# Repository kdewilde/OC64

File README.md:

# OC64
MX Compatible ortholinear PCB for the commodore case

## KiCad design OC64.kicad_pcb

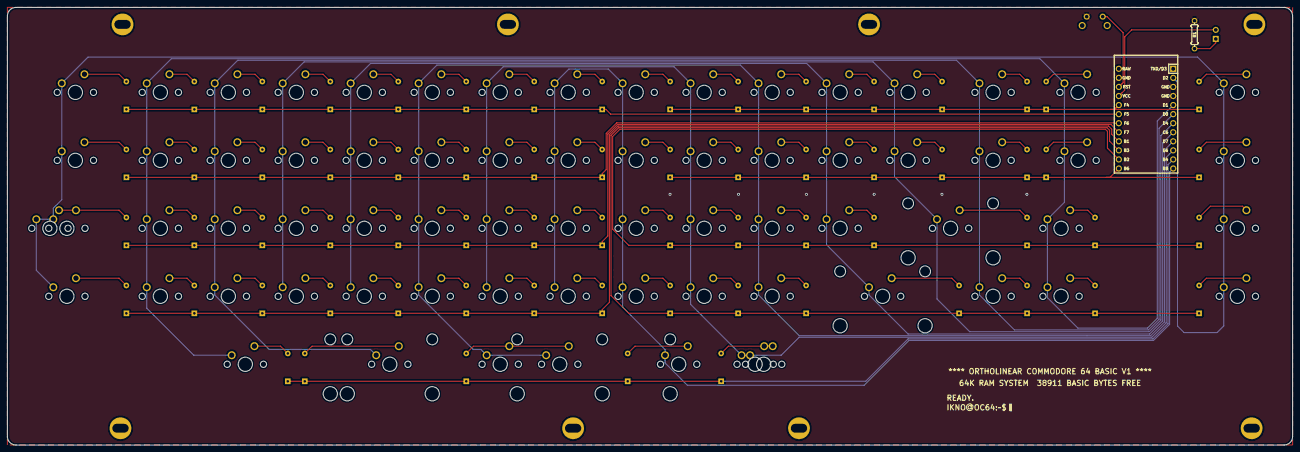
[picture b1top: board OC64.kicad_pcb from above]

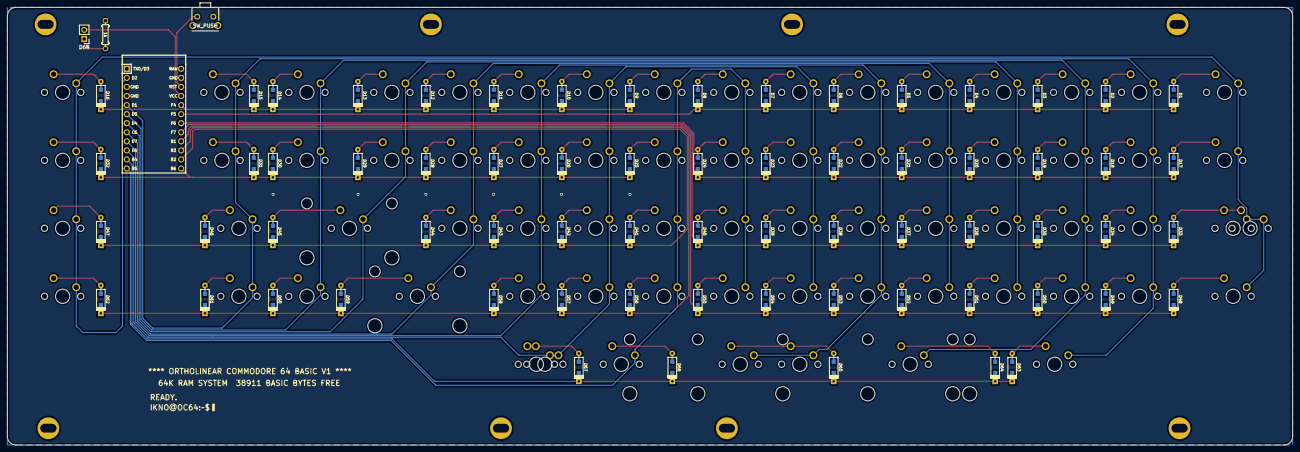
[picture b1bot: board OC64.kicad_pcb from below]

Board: 2 copper layers, 360.2 x 122.6 mm, 149 parts (71 on the bottom side), 88 nets.

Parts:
D1, D2, D3, D4, D5, D6, D7, D8, D9, D10, D11, D12, D13, D14, D15, D16, D17, D18, D19, D20, D21, D22, D23, D24, D25, D26, D27, D28, D29, D30, D31, D32, D33, D34, D35, D36, D37, D38, D39, D40, D41, D42, D43, D44, D45, D46, D47, D48, D49, D50, D51, D52, D53, D54, D55, D56, D57, D58, D59, D60, D61, D62, D63, D64, D65, D66, D67: D; D_SOD123_axial
D68: LED; PinHeader_1x02_P2.54mm_Vertical
H1, H2, H3, H4, H5, H6, H7, H8: MountingHole; Poker_oval_hole
R1: 1k; Resistor-Compact
RSW1: SW_PUSH; SW_TACT_TH_HORIZ
SW1: SW_ESC; MXOnly-1.5U
SW2: SW_1; MXOnly-1U
SW3: SW_2; MXOnly-1U
SW4: SW_3; MXOnly-1U
SW5: SW_4; MXOnly-1U
SW6: SW_5; MXOnly-1U
SW7: SW_6; MXOnly-1U
SW8: SW_7; MXOnly-1U
SW9: SW_8; MXOnly-1U
SW10: SW_9; MXOnly-1U
SW11: SW_0; MXOnly-1U
SW12: SW_-; MXOnly-1U
SW13: SW_=; MXOnly-1U
SW14: SW_BACK; MXOnly-1.5U
SW15: SW_DEL; MXOnly-1U
SW16: SW_F1; MXOnly-1.5U
SW17: SW_TAB; MXOnly-1.5U
SW18: SW_Q; MXOnly-1U
SW19: SW_W; MXOnly-1U
SW20: SW_E; MXOnly-1U
SW21: SW_R; MXOnly-1U
SW22: SW_T; MXOnly-1U
SW23: SW_Y; MXOnly-1U
SW24: SW_U; MXOnly-1U
SW25: SW_I; MXOnly-1U
SW26: SW_O; MXOnly-1U
SW27: SW_P; MXOnly-1U
SW28: SW_[; MXOnly-1U
SW29: SW_]; MXOnly-1U
SW30: SW_\; MXOnly-1.5U
SW31: SW_PGUP; MXOnly-1U
SW32: SW_F2; MXOnly-1.5U
SW33-1: SW_STPCAP; MXOnly-1.75USTEPPED
SW33-2: SW_CAPS; MXOnly-1.75U
SW34: SW_A; MXOnly-1U
SW35: SW_S; MXOnly-1U
SW36: SW_D; MXOnly-1U
SW37: SW_F; MXOnly-1U
SW38: SW_G; MXOnly-1U
SW39: SW_H; MXOnly-1U
SW40: SW_J; MXOnly-1U
SW41: SW_K; MXOnly-1U
SW42: SW_L; MXOnly-1U
SW43: SW_;; MXOnly-1U
SW44: SW_'; MXOnly-1U
SW45: SW_RET; MXOnly-2.25U
SW46: SW_PGDN; MXOnly-1U
SW47: SW_F3; MXOnly-1.5U
SW48: SW_SHIFT; MXOnly-1.75U
SW49: SW_Z; MXOnly-1U
SW50: SW_X; MXOnly-1U
SW51: SW_C; MXOnly-1U
SW52: SW_V; MXOnly-1U
SW53: SW_B; MXOnly-1U
SW54: SW_N; MXOnly-1U
SW55: SW_M; MXOnly-1U
SW56: SW_,; MXOnly-1U
SW57: SW_.; MXOnly-1U
SW58: SW_/; MXOnly-1U
SW59: SW_SHIFT; MXOnly-2.25U
SW60: SW_HOME; MXOnly-1U
SW61: SW_END; MXOnly-1U
SW62: SW_F4; MXOnly-1.5U
SW63: SW_CTRL; MXOnly-1.5U
SW64: SW_LSPAC; MXOnly-2.75U
SW65-1: SW_SPACE; MXOnly-6U
SW65-2: SW_RSPAC; MXOnly-2.25U
SW66: SW_ALT; MXOnly-1.25U
SW67-1: SW_META; MXOnly-1.25U
SW67-2: SW_META; MXOnly-1.5U
U1: ProMicro; ArduinoProMicro

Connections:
GND: R1.1, RSW1.2, U1.3, U1.4, U1.23
unnamed: D1.2, SW1.2
unnamed: D2.2, SW2.2
unnamed: D3.2, SW3.2
unnamed: D4.2, SW4.2
unnamed: D5.2, SW5.2
unnamed: D6.2, SW6.2
unnamed: D7.2, SW7.2
unnamed: D8.2, SW8.2
unnamed: D9.2, SW9.2
unnamed: D10.2, SW10.2
unnamed: D11.2, SW11.2
unnamed: D12.2, SW12.2
unnamed: D13.2, SW13.2
unnamed: D14.2, SW14.2
unnamed: D15.2, SW15.2
unnamed: D16.2, SW16.2
unnamed: D17.2, SW17.2
unnamed: D18.2, SW18.2
unnamed: D19.2, SW19.2
unnamed: D20.2, SW20.2
unnamed: D21.2, SW21.2
unnamed: D22.2, SW22.2
unnamed: D23.2, SW23.2
unnamed: D24.2, SW24.2
unnamed: D25.2, SW25.2
unnamed: D26.2, SW26.2
unnamed: D27.2, SW27.2
unnamed: D28.2, SW28.2
unnamed: D29.2, SW29.2
unnamed: D30.2, SW30.2
unnamed: D31.2, SW31.2
unnamed: D32.2, SW32.2
unnamed: D33.2, SW33-1.2, SW33-2.2
unnamed: D34.2, SW34.2
unnamed: D35.2, SW35.2
unnamed: D36.2, SW36.2
unnamed: D37.2, SW37.2
unnamed: D38.2, SW38.2
unnamed: D39.2, SW39.2
unnamed: D40.2, SW40.2
unnamed: D41.2, SW41.2
unnamed: D42.2, SW42.2
unnamed: D43.2, SW43.2
unnamed: D44.2, SW44.2
unnamed: D45.2, SW45.2
unnamed: D46.2, SW46.2
unnamed: D47.2, SW47.2
unnamed: D48.2, SW48.2
unnamed: D49.2, SW49.2
unnamed: D50.2, SW50.2
unnamed: D51.2, SW51.2
unnamed: D52.2, SW52.2
unnamed: D53.2, SW53.2
unnamed: D54.2, SW54.2
unnamed: D55.2, SW55.2
unnamed: D56.2, SW56.2
unnamed: D57.2, SW57.2
unnamed: D58.2, SW58.2
unnamed: D59.2, SW59.2
unnamed: D60.2, SW60.2
unnamed: D61.2, SW61.2
unnamed: D62.2, SW62.2
unnamed: D63.2, SW63.2
unnamed: D64.2, SW64.2
unnamed: D65.2, SW65-1.2, SW65-2.2
unnamed: D66.2, SW66.2
unnamed: D67.2, SW67-1.2, SW67-2.2
unnamed: D68.1, R1.2
VCC: D68.2, U1.21
col0: SW1.1, SW16.1, SW17.1, SW32.1, SW33-1.1, SW33-2.1, SW47.1, SW48.1, SW62.1, U1.2
col1: SW2.1, SW15.1, SW18.1, SW31.1, SW34.1, SW46.1, SW49.1, SW61.1, SW63.1, U1.5
col2: SW3.1, SW14.1, SW19.1, SW30.1, SW35.1, SW50.1, SW60.1, SW64.1, U1.6
col3: SW4.1, SW13.1, SW20.1, SW29.1, SW36.1, SW45.1, SW51.1, U1.7
col4: SW5.1, SW12.1, SW21.1, SW28.1, SW37.1, SW44.1, SW52.1, SW59.1, U1.8
col5: SW6.1, SW11.1, SW22.1, SW27.1, SW38.1, SW43.1, SW53.1, SW58.1, SW65-1.1, SW65-2.1, U1.9
col6: SW7.1, SW10.1, SW23.1, SW26.1, SW39.1, SW42.1, SW54.1, SW57.1, SW67-1.1, SW67-2.1, U1.10
col7: SW8.1, SW9.1, SW24.1, SW25.1, SW40.1, SW41.1, SW55.1, SW56.1, SW66.1, U1.12
reset: RSW1.1, U1.22
row0: D1.1, D2.1, D3.1, D4.1, D5.1, D6.1, D7.1, D8.1, U1.19
row1: D9.1, D10.1, D11.1, D12.1, D13.1, D14.1, D15.1, D16.1, U1.20
row2: D17.1, D18.1, D19.1, D20.1, D21.1, D22.1, D23.1, D24.1, U1.18
row3: D25.1, D26.1, D27.1, D28.1, D29.1, D30.1, D31.1, D32.1, U1.13
row4: D33.1, D34.1, D35.1, D36.1, D37.1, D38.1, D39.1, D40.1, U1.17
row5: D41.1, D42.1, D43.1, D44.1, D45.1, D46.1, D47.1, U1.14
row6: D48.1, D49.1, D50.1, D51.1, D52.1, D53.1, D54.1, D55.1, U1.16
row7: D56.1, D57.1, D58.1, D59.1, D60.1, D61.1, D62.1, U1.15
row8: D63.1, D64.1, D65.1, D66.1, D67.1, U1.11

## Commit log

2019-03-12 Added led pin & a text
2019-03-16 updated header pin for the LED to be on the correct side
